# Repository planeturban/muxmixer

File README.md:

# muxmixer

Arduino implemtation of audio separation solution described here: https://vintageisthenewold.com/amiga-audio-separation-solution/

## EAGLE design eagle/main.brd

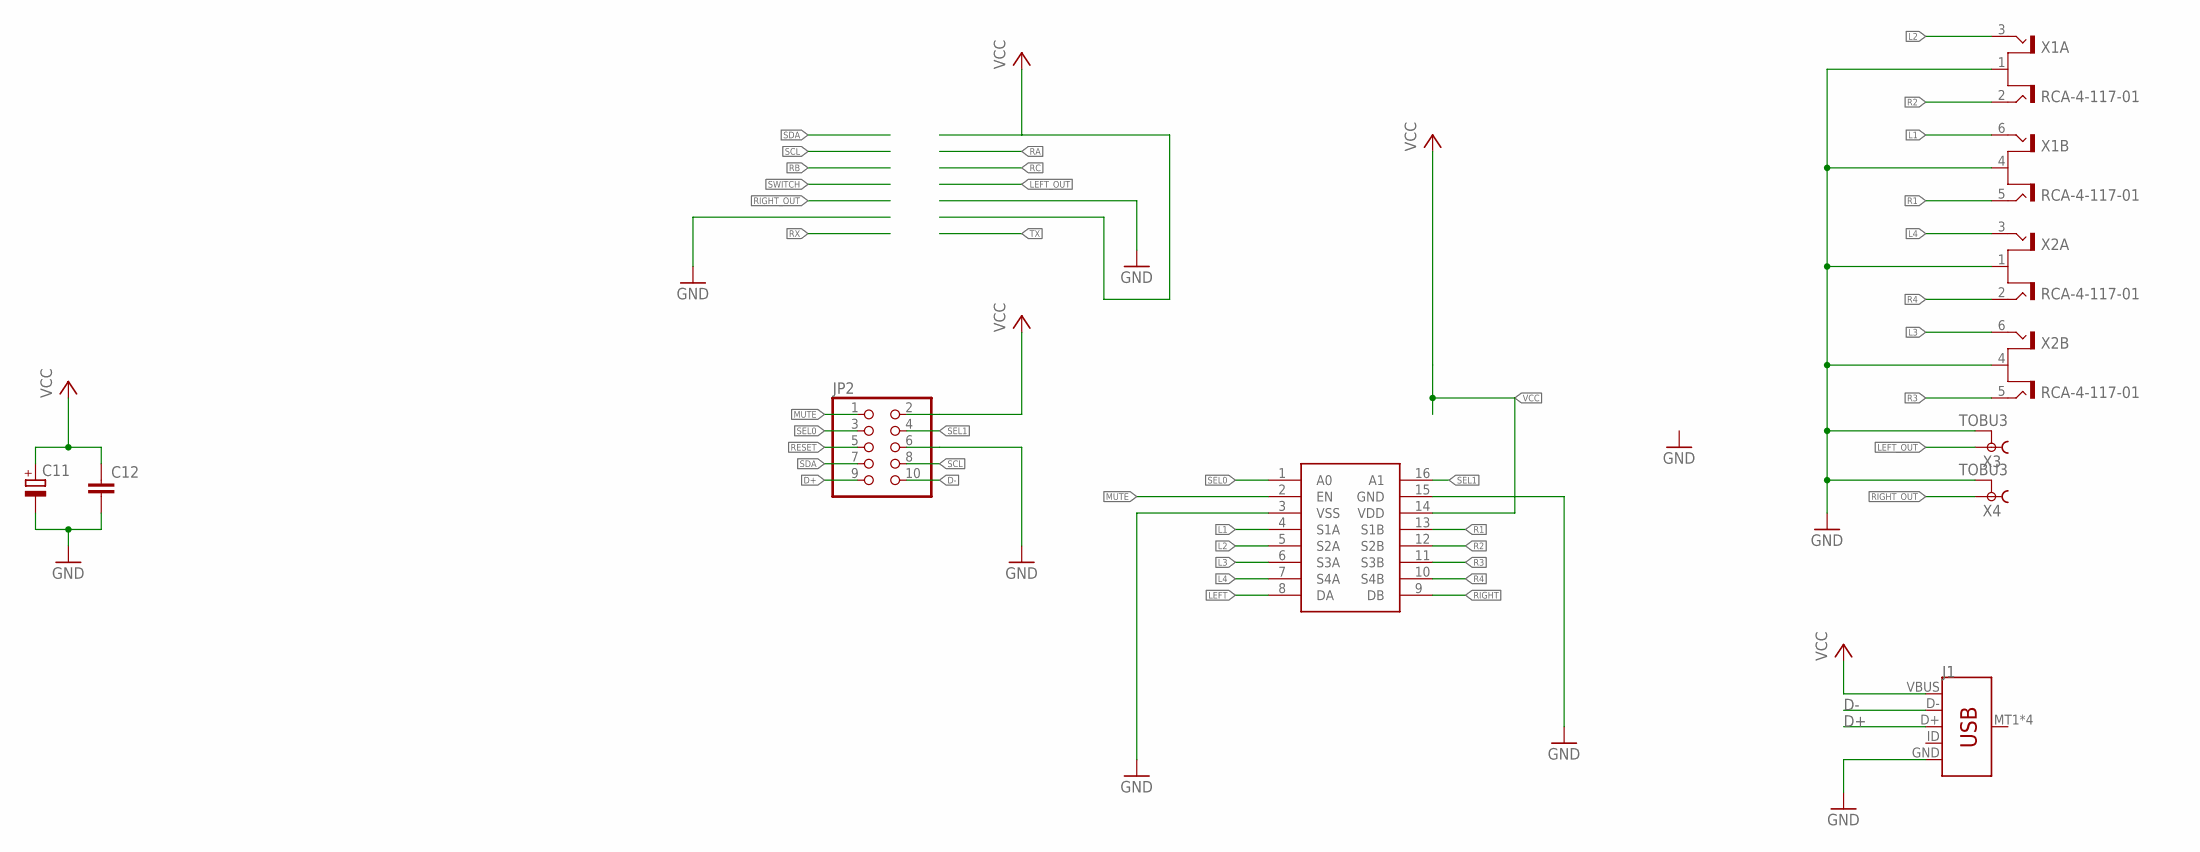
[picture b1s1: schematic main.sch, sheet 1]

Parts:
C11: 47uF; PANASONIC_D
C12: C-EUC1206; C1206
J1: USB_MICRO-B_SMT; USB-MICROB
JP2: PINHD-2X5; 2X05
U2: ADG709; TSSOP-16
X1, X2: RCA-4-117-01
X3, X4: TOBU3

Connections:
D+: J1.D+, JP2.9
D-: J1.D-, JP2.10
GND: C11.-, C12.2, J1.GND, JP2.6, U2.3 (VSS), U2.15 (GND), X1.1 (S), X1.4 (S), X2.1 (S), X2.4 (S), X3.2, X3.2@1 (2), X3.2@2 (2), X4.2, X4.2@1 (2), X4.2@2 (2); also elsewhere on the board
L1: U2.4 (S1A), X1.6 (T2)
L2: U2.5 (S2A), X1.3 (T2)
L3: U2.6 (S3A), X2.6 (T2)
L4: U2.7 (S4A), X2.3 (T2)
LEFT: U2.8 (DA); also elsewhere on the board
LEFT_OUT: X3.1; also elsewhere on the board
MUTE: JP2.1, U2.2 (EN)
R1: U2.13 (S1B), X1.5 (T1)
R2: U2.12 (S2B), X1.2 (T1)
R3: U2.11 (S3B), X2.5 (T1)
R4: U2.10 (S4B), X2.2 (T1)
RESET: JP2.5
RIGHT: U2.9 (DB); also elsewhere on the board
RIGHT_OUT: X4.1; also elsewhere on the board
SCL: JP2.8; also elsewhere on the board
SDA: JP2.7; also elsewhere on the board
SEL0: JP2.3, U2.1 (A0)
SEL1: JP2.4, U2.16 (A1)
VCC: C11.+, C12.1, J1.VBUS, JP2.2, U2.14 (VDD); also elsewhere on the board

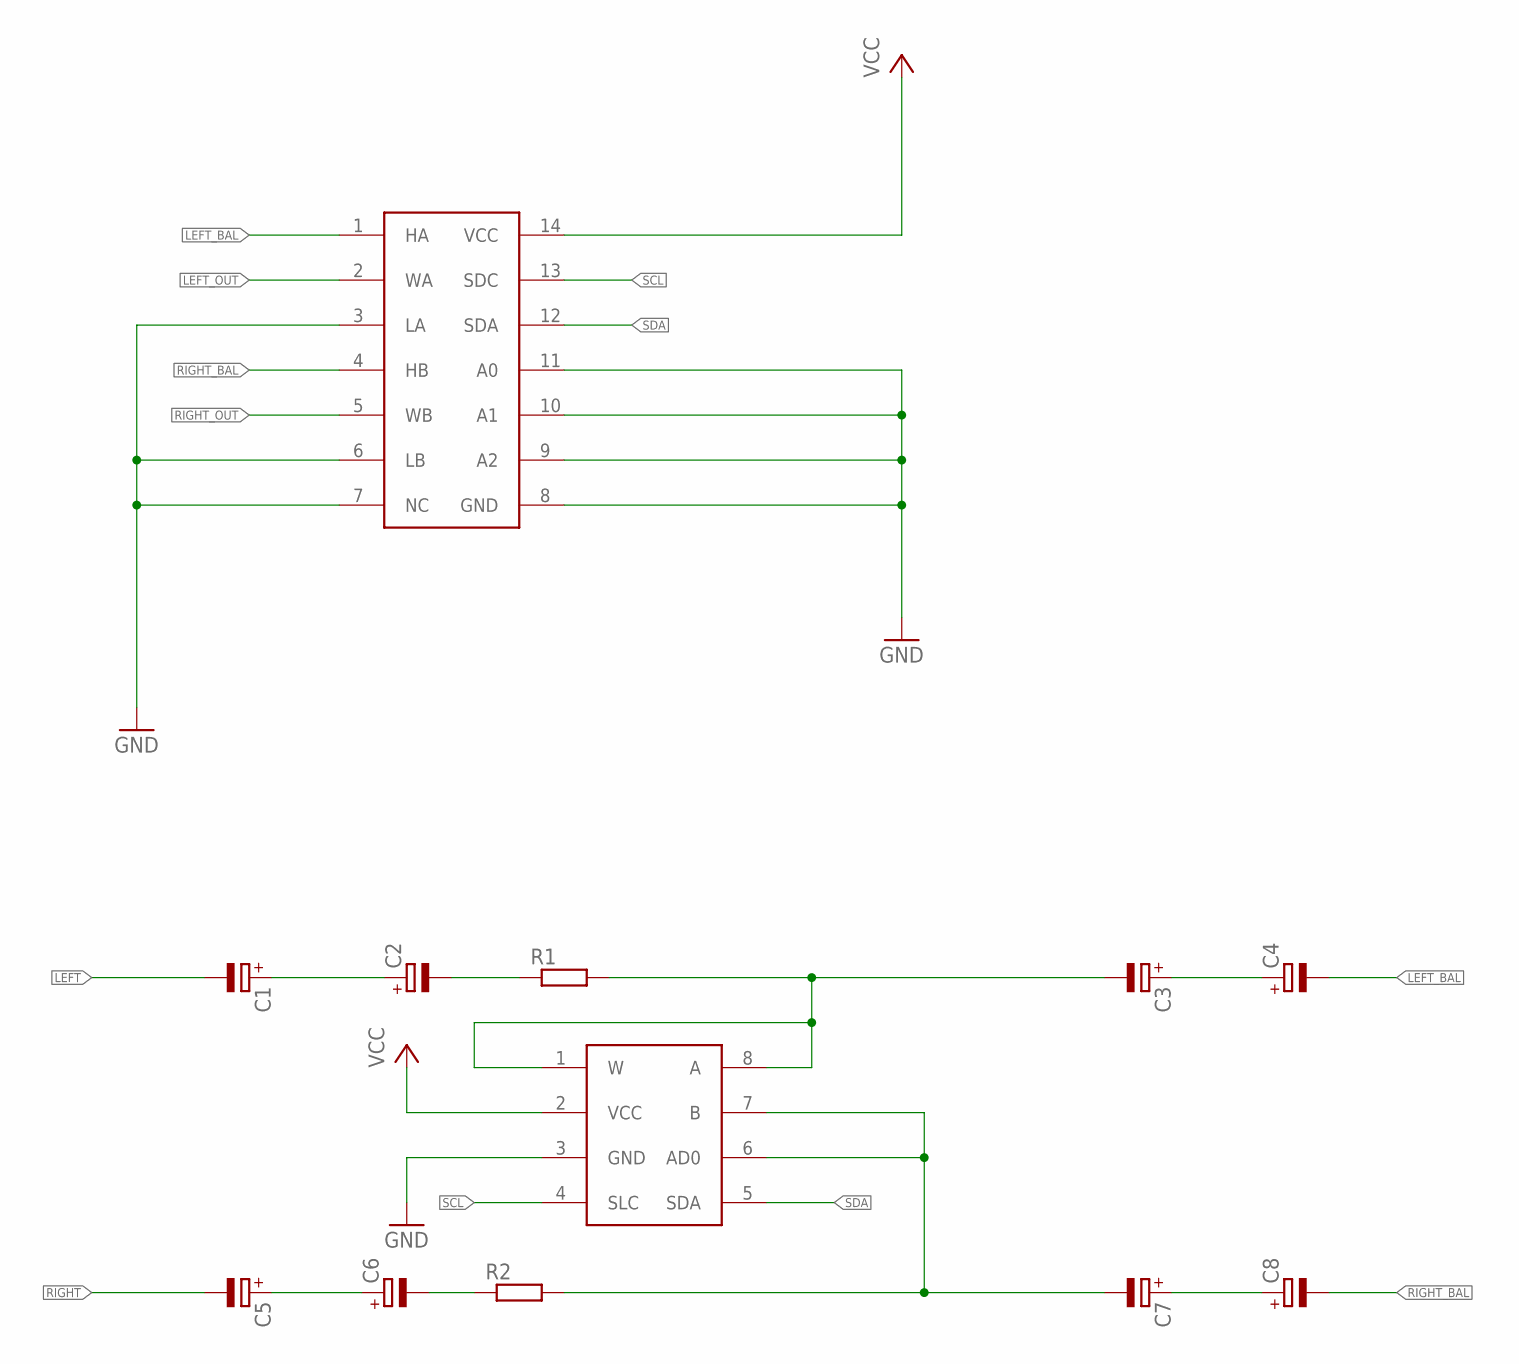
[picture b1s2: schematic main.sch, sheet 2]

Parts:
C1, C2, C3, C4, C5, C6, C7, C8: 47uF; PANASONIC_D
R1, R2: R-EU_M1206; M1206
U3: AD5273; SOT23-8
U4: MAX5387; TSSOP-14

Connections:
GND: U3.3 (GND), U4.3 (LA), U4.6 (LB), U4.7 (NC), U4.8 (GND), U4.9 (A2), U4.10 (A1), U4.11 (A0); also elsewhere on the board
LEFT: C1.-; also elsewhere on the board
LEFT_BAL: C4.-, U4.1 (HA)
LEFT_OUT: U4.2 (WA); also elsewhere on the board
unnamed: C1.+, C2.+
unnamed: C5.+, C6.+
unnamed: C7.-, R2.2, U3.6 (AD0), U3.7 (B)
unnamed: C7.+, C8.+
unnamed: C3.+, C4.+
unnamed: C2.-, R1.1
unnamed: C3.-, R1.2, U3.1 (W), U3.8 (A)
unnamed: C6.-, R2.1
RIGHT: C5.-; also elsewhere on the board
RIGHT_BAL: C8.-, U4.4 (HB)
RIGHT_OUT: U4.5 (WB); also elsewhere on the board
SCL: U3.4 (SLC), U4.13 (SDC); also elsewhere on the board
SDA: U3.5 (SDA), U4.12 (SDA); also elsewhere on the board
VCC: U3.2 (VCC), U4.14 (VCC); also elsewhere on the board

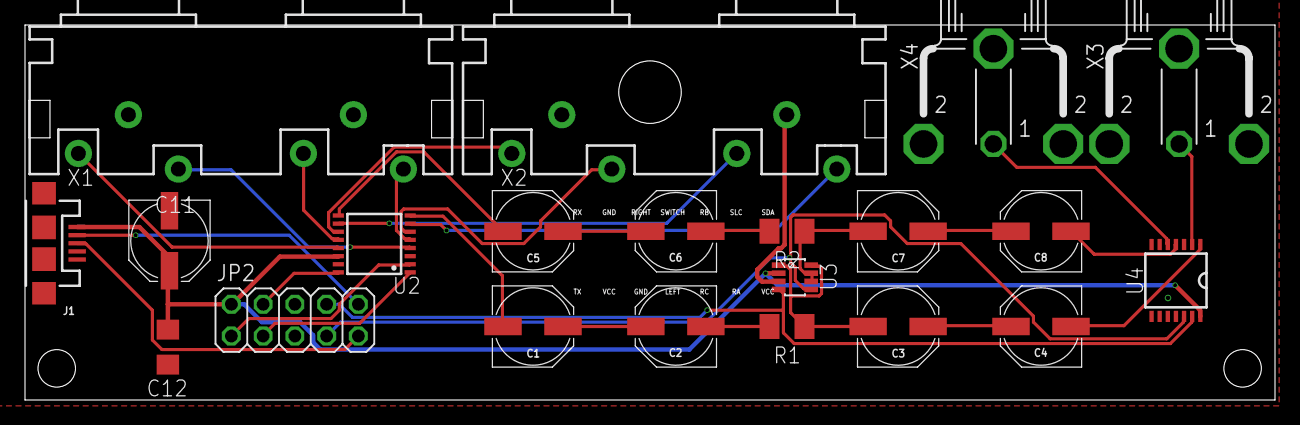
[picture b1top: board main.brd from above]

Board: 2 copper layers, 100.0 x 30.0 mm, 21 parts (0 on the bottom side), 31 nets.

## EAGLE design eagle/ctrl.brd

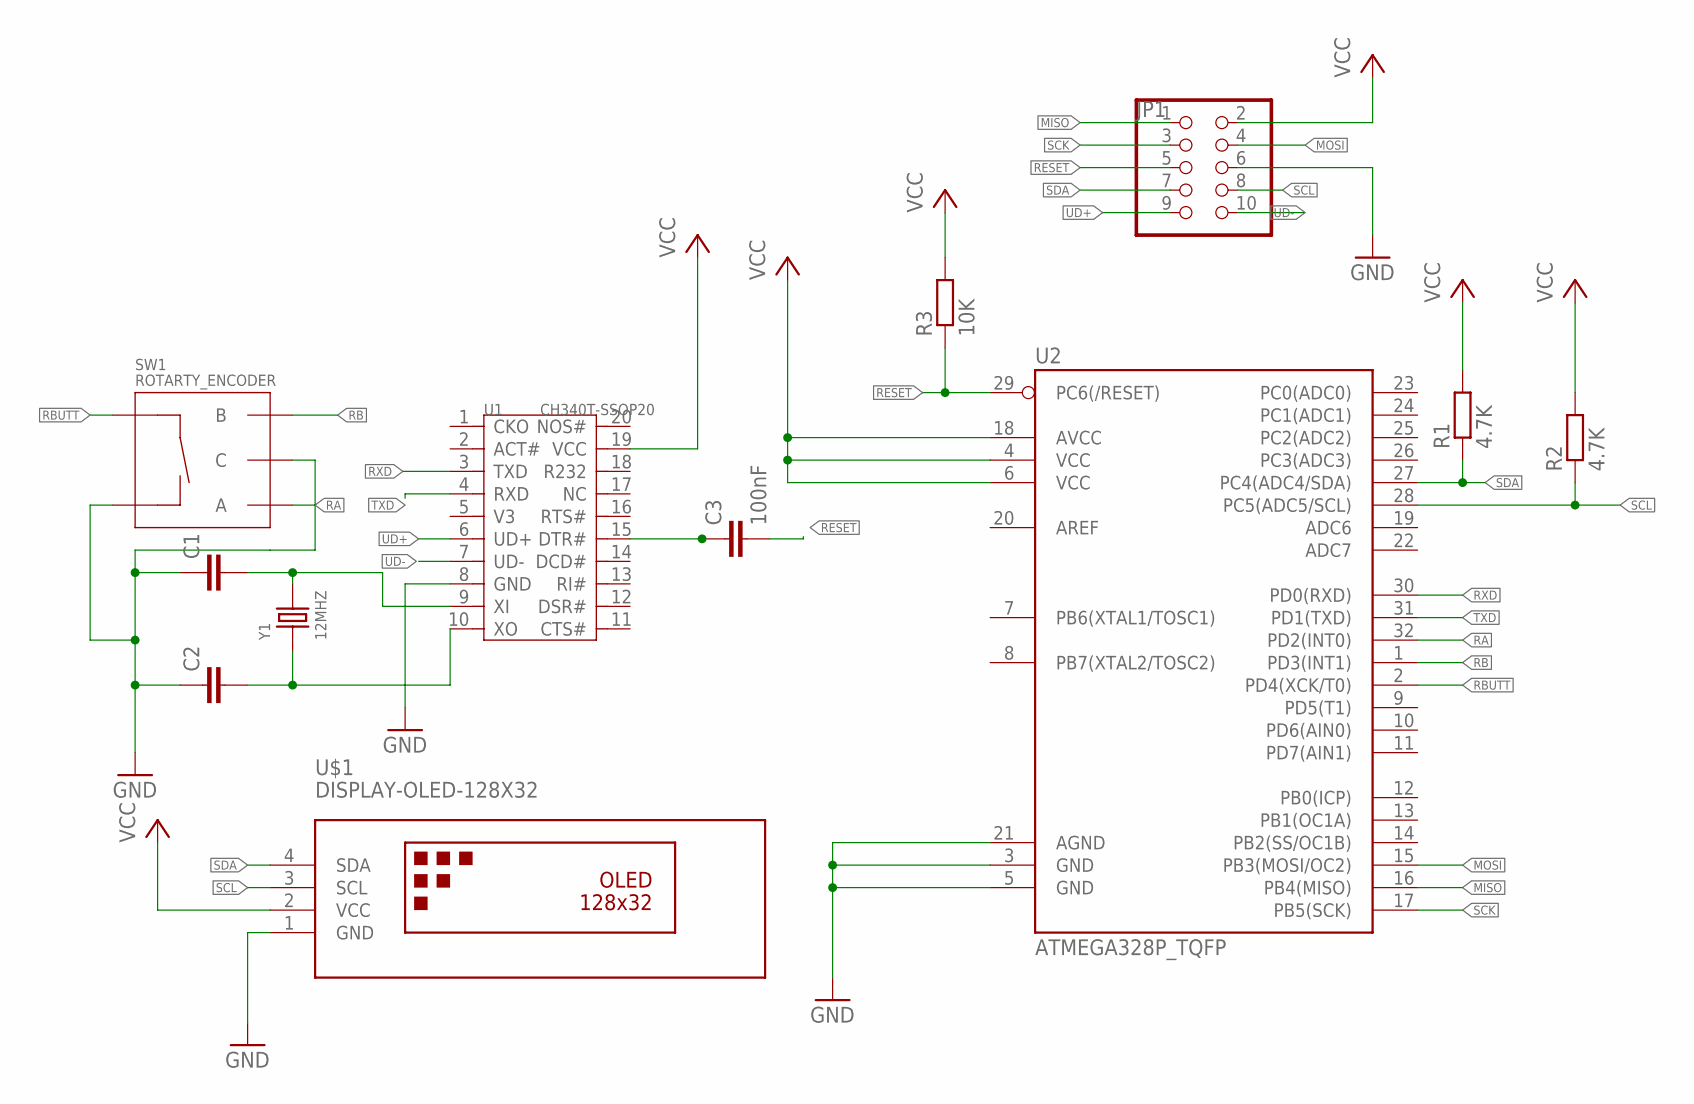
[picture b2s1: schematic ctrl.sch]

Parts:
C1, C2: C-EUC0805; C0805
C3: 100nF; C0805
JP1: PINHD-2X5; 2X05
R1, R2: 4.7K; M0805
R3: 10K; M0805
SW1: ROTARTY_ENCODER; ROTARY_ENC_PLAIN
U1: CH340T-SSOP20; SSOP20-0.65-7.6X5.2MM
U2: ATMEGA328P_TQFP; TQFP32-08
U$1: DISPLAY-OLED-128X32
Y1: 12MHZ; X2-SMD-5.0X3.2X1.3MM

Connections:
GND: C1.1, C2.1, JP1.6, SW1.C, SW1.SW-, U1.8 (GND), U2.3 (GND), U2.5 (GND), U2.21 (AGND), U$1.1 (GND)
MISO: JP1.1, U2.16 (PB4(MISO))
MOSI: JP1.4, U2.15 (PB3(MOSI/OC2))
unnamed: C1.2, U1.9 (XI), Y1.2
unnamed: C3.1, U1.15 (DTR#)
unnamed: C2.2, U1.10 (XO), Y1.1
RA: SW1.A, U2.32 (PD2(INT0))
RB: SW1.B, U2.1 (PD3(INT1))
RBUTT: SW1.SW+, U2.2 (PD4(XCK/T0))
RESET: C3.2, JP1.5, R3.1, U2.29 (PC6(/RESET))
RXD: U1.3 (TXD), U2.30 (PD0(RXD))
SCK: JP1.3, U2.17 (PB5(SCK))
SCL: JP1.8, R2.1, U2.28 (PC5(ADC5/SCL)), U$1.3 (SCL)
SDA: JP1.7, R1.1, U2.27 (PC4(ADC4/SDA)), U$1.4 (SDA)
TXD: U1.4 (RXD), U2.31 (PD1(TXD))
UD+: JP1.9, U1.6 (UD+)
UD-: JP1.10, U1.7 (UD-)
VCC: JP1.2, R1.2, R2.2, R3.2, U1.19 (VCC), U2.4 (VCC), U2.6 (VCC), U2.18 (AVCC), U$1.2 (VCC)

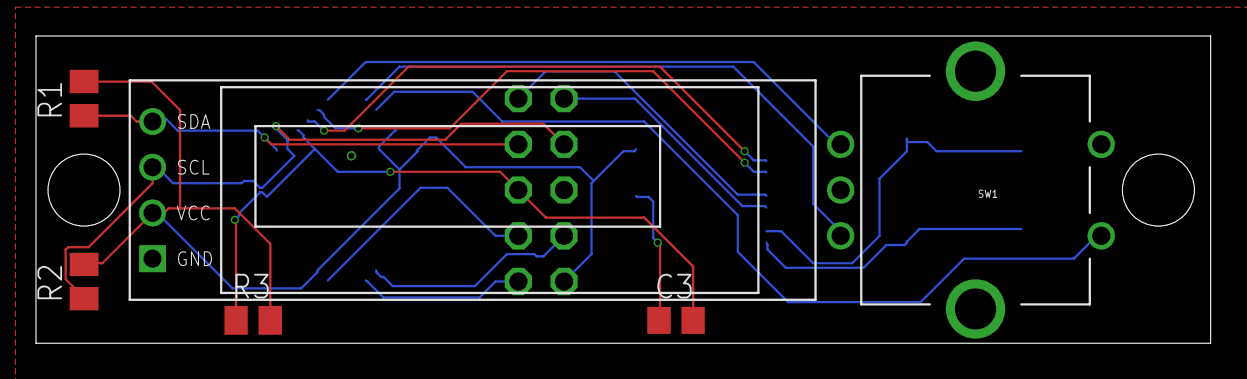
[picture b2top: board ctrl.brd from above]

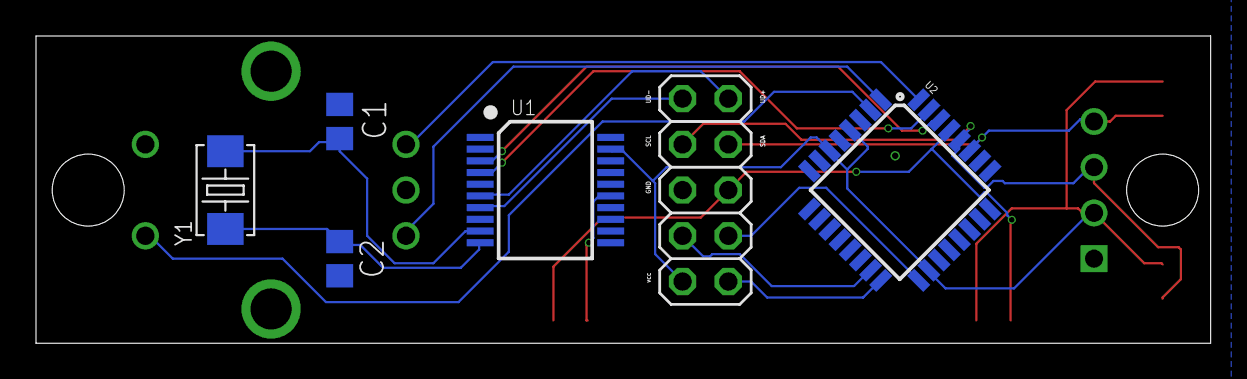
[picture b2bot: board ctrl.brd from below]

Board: 2 copper layers, 65.3 x 17.1 mm, 12 parts (6 on the bottom side), 18 nets.

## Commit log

2019-10-26 Docs.
2019-10-27 We've got a menu system.
2019-11-01 Added pots.
2019-11-11 To compensate for my bad soldering skills..
2019-11-11 Eagle files

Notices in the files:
parts and their libraries:
SparkFun-Electromechanical: Licensing: Creative Commons ShareAlike 4.0 International - https://creativecommons.org/licenses/by-sa/4.0
diy-modules: Released under the Creative Commons Attribution 4.0 International License: http://creativecommons.org/licenses/by/4.0
